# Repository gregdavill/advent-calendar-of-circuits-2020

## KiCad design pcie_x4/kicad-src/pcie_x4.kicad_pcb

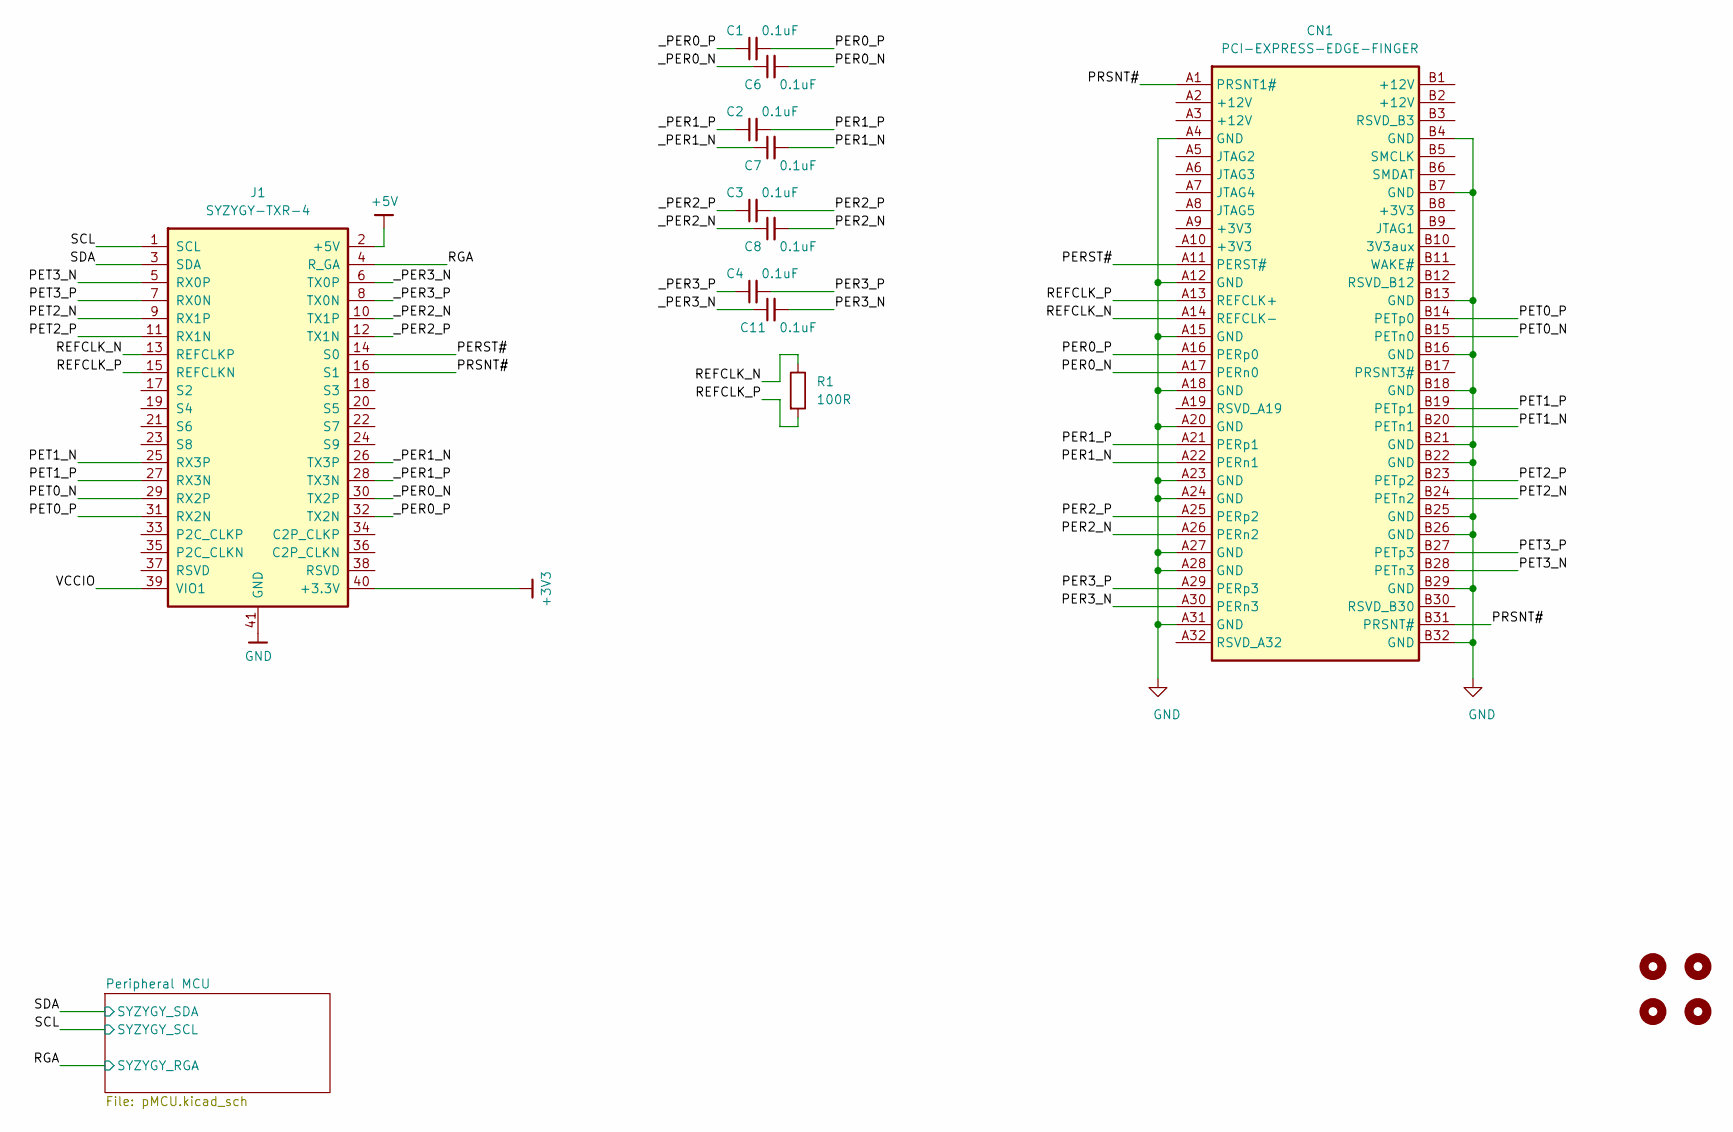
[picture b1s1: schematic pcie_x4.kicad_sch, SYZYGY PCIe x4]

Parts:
C1, C2, C3, C4, C6, C7, C8, C11: 0.1uF; C_0402_1005Metric
CN1: PCI-EXPRESS-EDGE-FINGER; BUS_PCIexpress_x4
H1, H2, H3, H4: MountingHole; MountingHole_3.2mm_M3
J1: SYZYGY-TXR-4; SYZYGY-TXR-POD
R1: 100R; R_0402_1005Metric

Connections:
+3V3: J1.40 (+3.3V); also elsewhere on the board
+5V: J1.2 (+5V)
/PER0_N: C6.2, CN1.A17 (PERn0)
/PER0_P: C1.2, CN1.A16 (PERp0)
/PER1_N: C7.2, CN1.A22 (PERn1)
/PER1_P: C2.2, CN1.A21 (PERp1)
/PER2_N: C8.2, CN1.A26 (PERn2)
/PER2_P: C3.2, CN1.A25 (PERp2)
/PER3_N: C11.2, CN1.A30 (PERn3)
/PER3_P: C4.2, CN1.A29 (PERp3)
/PERST#: CN1.A11 (PERST#), J1.14 (S0)
/PET0_N: CN1.B15 (PETn0), J1.29 (RX2P)
/PET0_P: CN1.B14 (PETp0), J1.31 (RX2N)
/PET1_N: CN1.B20 (PETn1), J1.25 (RX3P)
/PET1_P: CN1.B19 (PETp1), J1.27 (RX3N)
/PET2_N: CN1.B24 (PETn2), J1.9 (RX1P)
/PET2_P: CN1.B23 (PETp2), J1.11 (RX1N)
/PET3_N: CN1.B28 (PETn3), J1.5 (RX0P)
/PET3_P: CN1.B27 (PETp3), J1.7 (RX0N)
/PRSNT#: CN1.A1 (PRSNT1#), CN1.B31 (PRSNT#), J1.16 (S1)
/REFCLK_N: CN1.A14 (REFCLK-), J1.13 (REFCLKP), R1.1
/REFCLK_P: CN1.A13 (REFCLK+), J1.15 (REFCLKN), R1.2
/RGA: J1.4 (R_GA); also elsewhere on the board
/SCL: J1.1 (SCL); also elsewhere on the board
/SDA: J1.3 (SDA); also elsewhere on the board
/VCCIO: J1.39 (VIO1)
/_PER0_N: C6.1, J1.30 (TX2P)
/_PER0_P: C1.1, J1.32 (TX2N)
/_PER1_N: C7.1, J1.26 (TX3P)
/_PER1_P: C2.1, J1.28 (TX3N)
/_PER2_N: C8.1, J1.10 (TX1P)
/_PER2_P: C3.1, J1.12 (TX1N)
/_PER3_N: C11.1, J1.6 (TX0P)
/_PER3_P: C4.1, J1.8 (TX0N)
GND: CN1.A4 (GND), CN1.A12 (GND), CN1.A15 (GND), CN1.A18 (GND), CN1.A20 (GND), CN1.A23 (GND), CN1.A24 (GND), CN1.A27 (GND), CN1.A28 (GND), CN1.A31 (GND), CN1.B4 (GND), CN1.B7 (GND), CN1.B13 (GND), CN1.B16 (GND), CN1.B18 (GND), CN1.B21 (GND), CN1.B22 (GND), CN1.B25 (GND), CN1.B26 (GND), CN1.B29 (GND), CN1.B32 (GND), J1.41 (GND); also elsewhere on the board

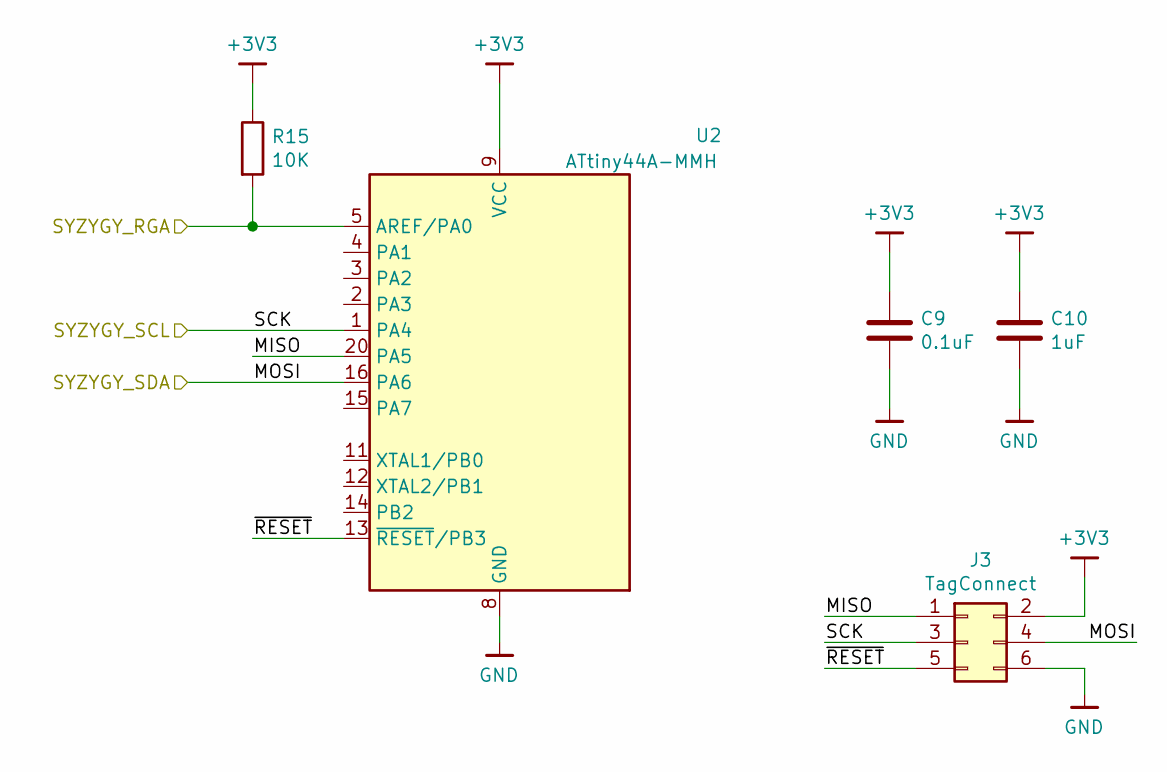
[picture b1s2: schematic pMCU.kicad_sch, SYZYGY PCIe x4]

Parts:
C9: 0.1uF; C_0402_1005Metric
C10: 1uF; C_0402_1005Metric
J3: TagConnect; TC2030-NL_SMALL
R15: 10K; R_0402_1005Metric
U2: ATtiny44A-MMH; QFN-20-1EP_3x3mm_P0.45mm_EP1.6x1.6mm

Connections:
+3V3: C9.1, C10.1, J3.2, R15.1, U2.9 (VCC); also elsewhere on the board
/Peripheral MCU/MISO: J3.1, U2.20 (PA5)
/Peripheral MCU/~RESET: J3.5, U2.13 (~RESET~/PB3)
/RGA: R15.2, U2.5 (AREF/PA0); also elsewhere on the board
/SCL: J3.3, U2.1 (PA4); also elsewhere on the board
/SDA: J3.4, U2.16 (PA6); also elsewhere on the board
GND: C9.2, C10.2, J3.6, U2.8 (GND), U2.21 (GND); also elsewhere on the board

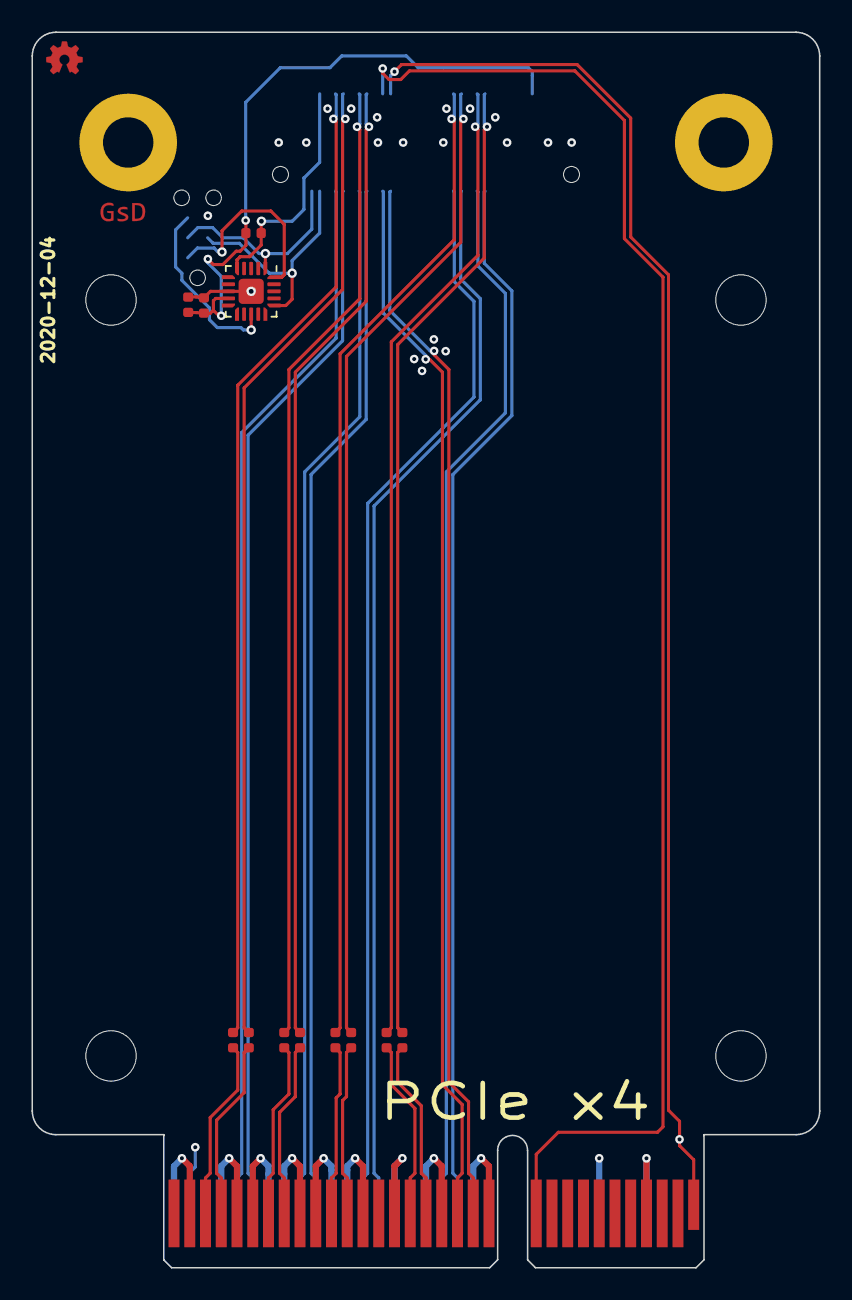
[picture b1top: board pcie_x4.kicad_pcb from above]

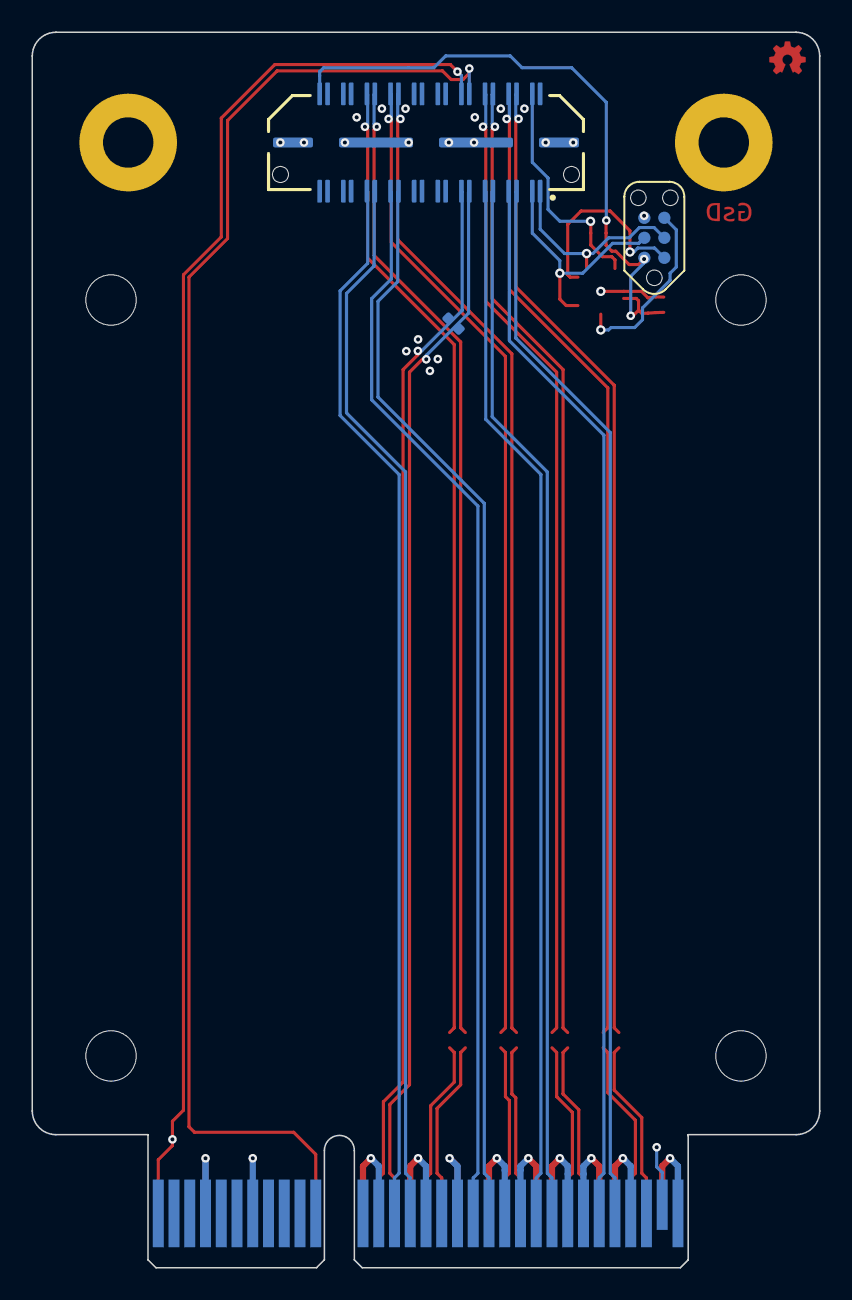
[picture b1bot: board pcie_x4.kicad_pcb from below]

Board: 4 copper layers, 50.0 x 78.5 mm, 20 parts (4 on the bottom side), 35 nets.

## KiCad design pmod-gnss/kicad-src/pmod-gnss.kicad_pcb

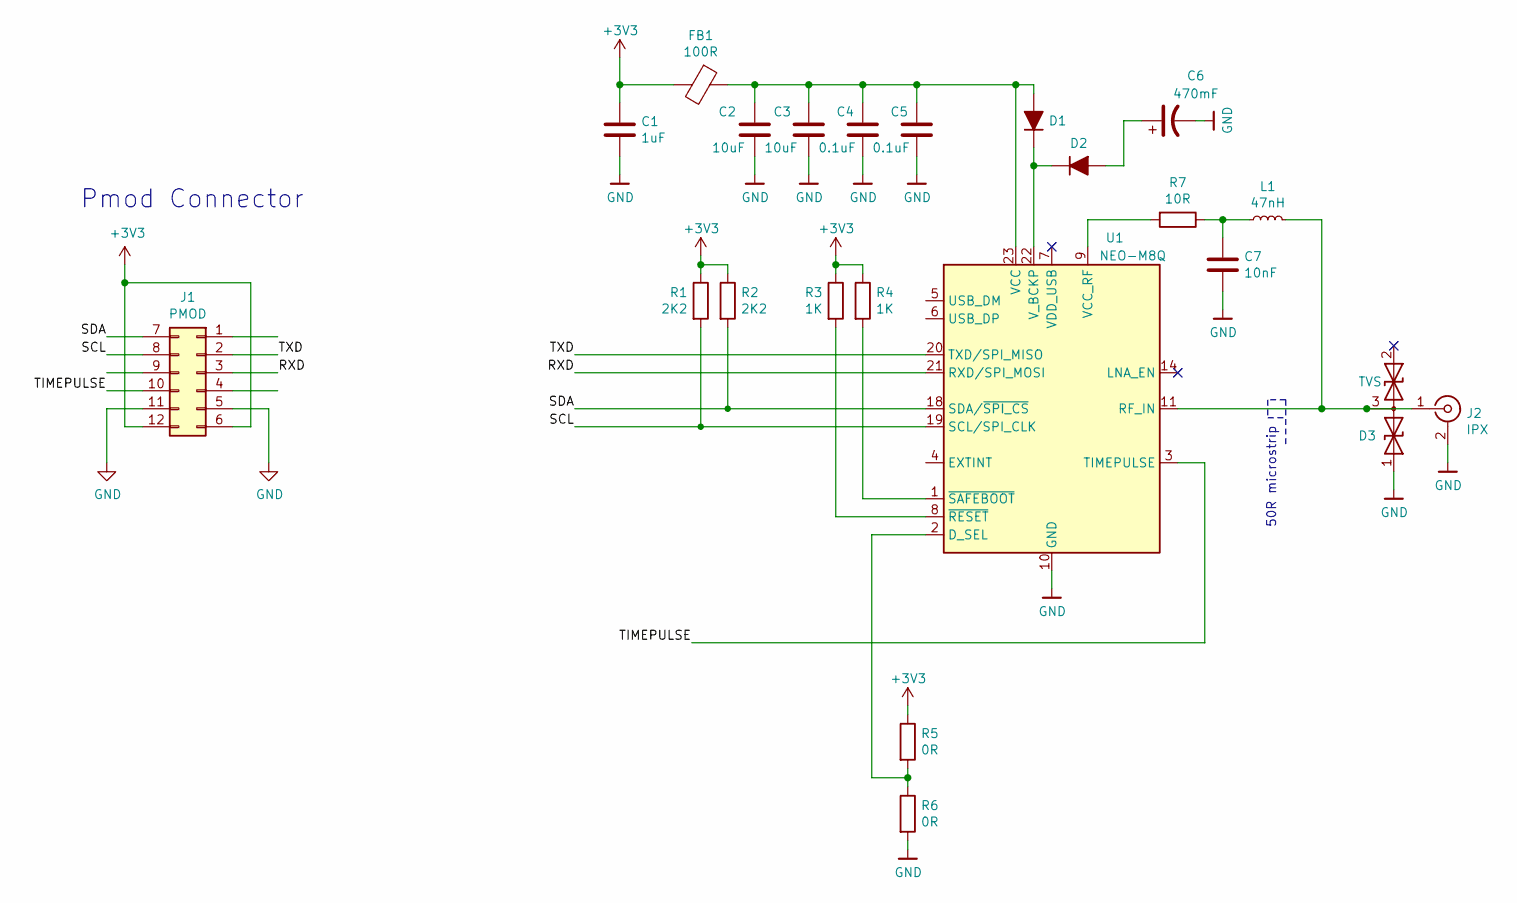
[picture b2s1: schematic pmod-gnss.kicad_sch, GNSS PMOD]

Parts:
C1: 1uF; C_0402_1005Metric
C2, C3: 10uF; C_0603_1608Metric
C4, C5: 0.1uF; C_0402_1005Metric
C6: 470mF; BatteryHolder_Keystone_2998_1x6.8mm
C7: 10nF; C_0402_1005Metric
D1, D2: D_ALT; D_SOD-123F
D3: TVS; SOT-323_SC-70
FB1: 100R; L_0603_1608Metric
J1: PMOD; PinHeader_2x06_P2.54mm_Horizontal
J2: IPX; SMA_Amphenol_132289_EdgeMount
L1: 47nH; L_0402_1005Metric
R1, R2: 2K2; R_0402_1005Metric
R3, R4: 1K; R_0402_1005Metric
R5, R6: 0R; R_0402_1005Metric
R7: 10R; R_0402_1005Metric
U1: NEO-M8Q; ublox_NEO

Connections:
+3V3: C1.1, FB1.2, J1.6, J1.12, R1.1, R2.1, R3.1, R4.1, R5.1
/RXD: J1.3, U1.21 (RXD/SPI_MOSI)
/SCL: J1.8, R1.2, U1.19 (SCL/SPI_CLK)
/SDA: J1.7, R2.2, U1.18 (SDA/~SPI_CS)
/TIMEPULSE: J1.10, U1.3 (TIMEPULSE)
/TXD: J1.2, U1.20 (TXD/SPI_MISO)
GND: C1.2, C2.2, C3.2, C4.2, C5.2, C6.2, C7.2, D3.1 (A1), J1.5, J1.11, J2.2 (Ext), R6.2, U1.10 (GND), U1.12 (GND), U1.13 (GND), U1.24 (GND)
unnamed: C2.1, C3.1, C4.1, C5.1, D1.2 (A), FB1.1, U1.23 (VCC)
unnamed: C6.1, D2.2 (A)
unnamed: C7.1, L1.1, R7.1
unnamed: D1.1 (K), D2.1 (K), U1.22 (V_BCKP)
unnamed: D3.3 (common), J2.1 (In), L1.2, U1.11 (RF_IN)
unnamed: R3.2, U1.8 (~RESET)
unnamed: R4.2, U1.1 (~SAFEBOOT)
unnamed: R5.2, R6.1, U1.2 (D_SEL)
unnamed: R7.2, U1.9 (VCC_RF)
no_connect_23: D3.2 (A2)
no_connect_24: U1.14 (LNA_EN)
no_connect_25: U1.15 (RESERVED)
no_connect_26: U1.16 (RESERVED)
no_connect_27: U1.17 (RESERVED)
no_connect_28: U1.7 (VDD_USB)

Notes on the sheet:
Pmod Connector
50R microstrip

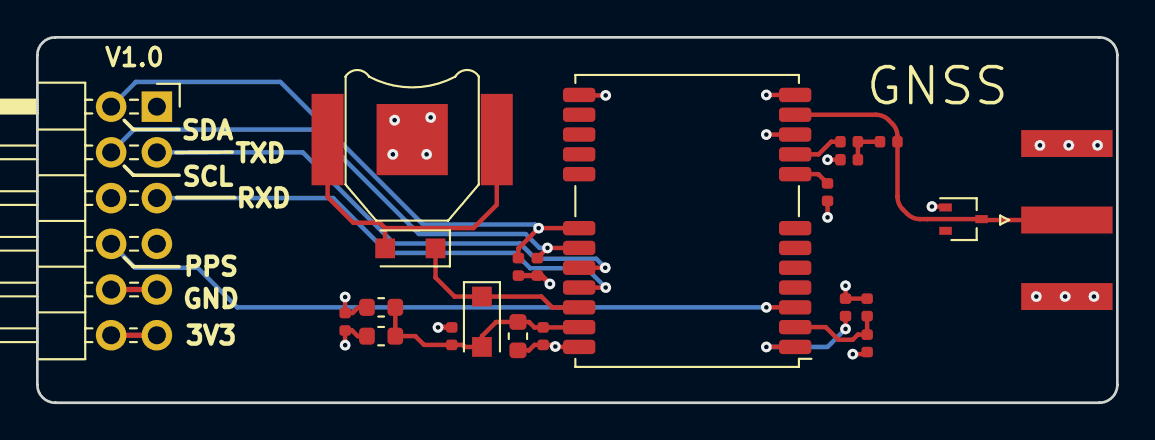
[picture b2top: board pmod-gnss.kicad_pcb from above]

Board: 4 copper layers, 60.0 x 20.3 mm, 22 parts (0 on the bottom side), 16 nets.

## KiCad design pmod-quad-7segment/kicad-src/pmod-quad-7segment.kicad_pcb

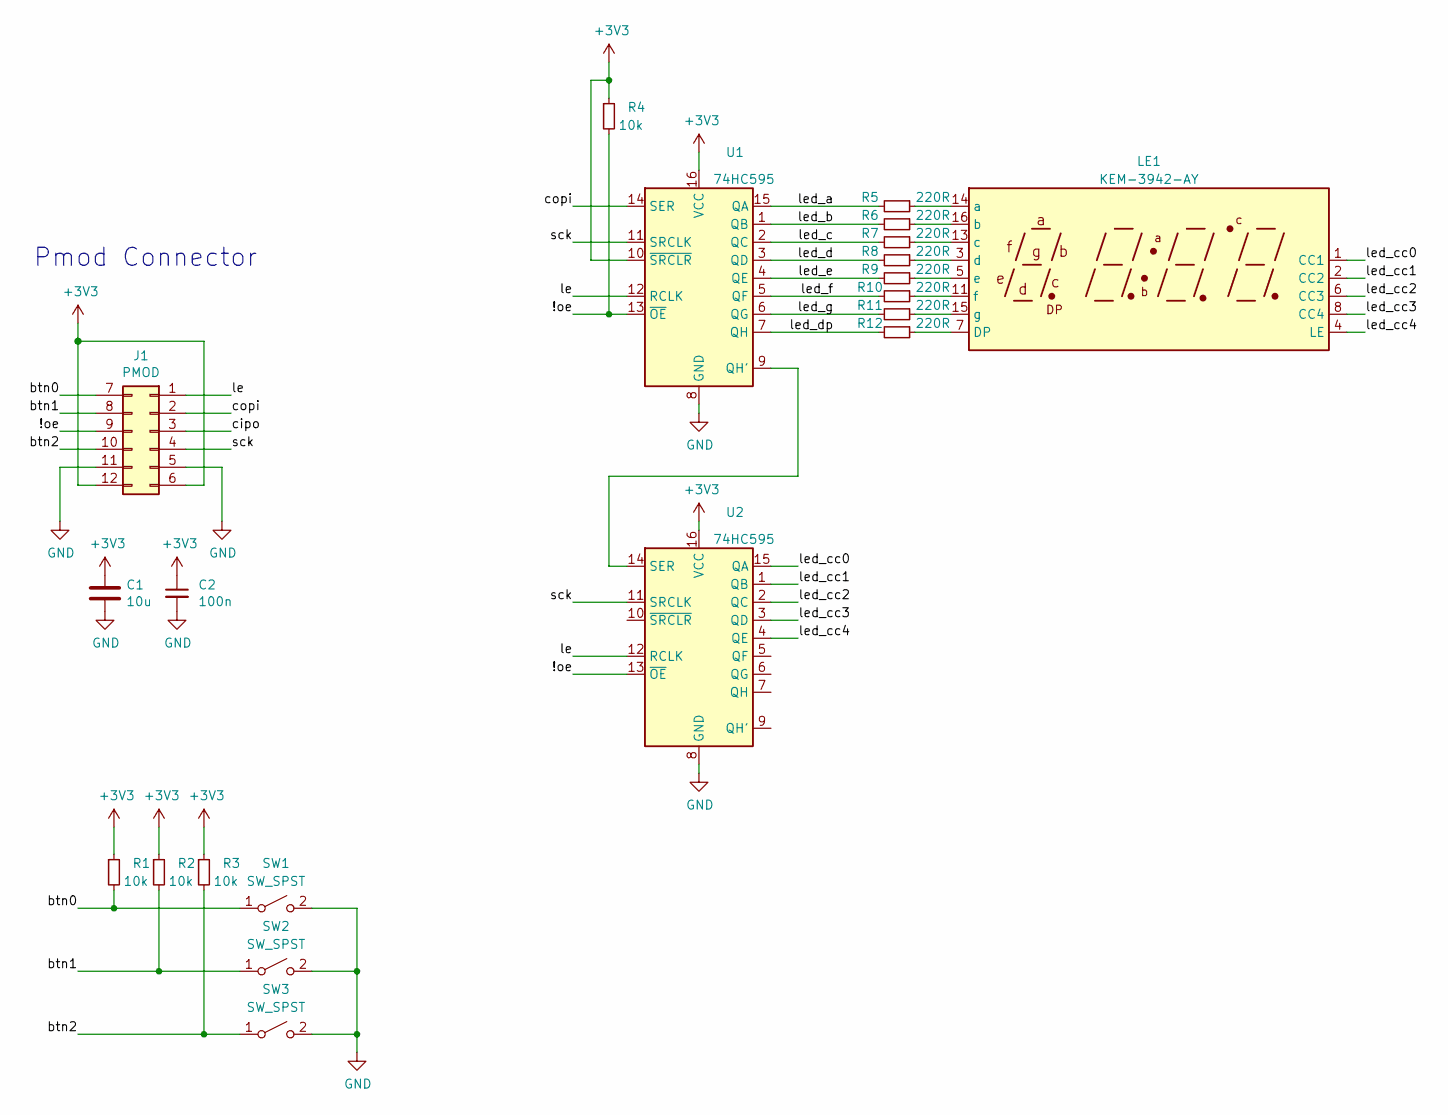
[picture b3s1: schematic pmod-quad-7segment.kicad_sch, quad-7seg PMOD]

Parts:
C1: 10u; C_0603_1608Metric
C2: 100n; C_0402_1005Metric
J1: PMOD; PinHeader_2x06_P2.54mm_Horizontal
LE1: KEM-3942-AY; kem-3942-ay
R1, R2, R3, R4: 10k; R_0402_1005Metric
R5, R6, R7, R8, R9, R10, R11, R12: 220R; R_0402_1005Metric
SW1, SW2, SW3: SW_SPST; SW_SPST_PTS810
U1, U2: 74HC595; TSSOP-16_4.4x5mm_P0.65mm

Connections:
+3V3: C1.1, C2.1, J1.6, J1.12, R1.1, R2.1, R3.1, R4.1, U1.10 (~SRCLR), U1.16 (VCC), U2.16 (VCC)
/!oe: J1.9, R4.2, U1.13 (~OE), U2.13 (~OE)
/btn0: J1.7, R1.2, SW1.1 (A)
/btn1: J1.8, R2.2, SW2.1 (A)
/btn2: J1.10, R3.2, SW3.1 (A)
/cipo: J1.3
/copi: J1.2, U1.14 (SER)
/le: J1.1, U1.12 (RCLK), U2.12 (RCLK)
/led_a: R5.2, U1.15 (QA)
/led_b: R6.2, U1.1 (QB)
/led_c: R7.2, U1.2 (QC)
/led_cc0: LE1.1 (CC1), U2.15 (QA)
/led_cc1: LE1.2 (CC2), U2.1 (QB)
/led_cc2: LE1.6 (CC3), U2.2 (QC)
/led_cc3: LE1.8 (CC4), U2.3 (QD)
/led_cc4: LE1.4 (LE), U2.4 (QE)
/led_d: R8.2, U1.3 (QD)
/led_dp: R12.2, U1.7 (QH)
/led_e: R9.2, U1.4 (QE)
/led_f: R10.2, U1.5 (QF)
/led_g: R11.2, U1.6 (QG)
/sck: J1.4, U1.11 (SRCLK), U2.11 (SRCLK)
GND: C1.2, C2.2, J1.5, J1.11, SW1.2 (B), SW2.2 (B), SW3.2 (B), U1.8 (GND), U2.8 (GND)
unnamed: LE1.3 (d), R8.1
unnamed: LE1.5 (e), R9.1
unnamed: LE1.7 (DP), R12.1
unnamed: LE1.11 (f), R10.1
unnamed: LE1.13 (c), R7.1
unnamed: LE1.14 (a), R5.1
unnamed: LE1.15 (g), R11.1
unnamed: LE1.16 (b), R6.1
unnamed: U1.9 (QH'), U2.14 (SER)

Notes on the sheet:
Pmod Connector

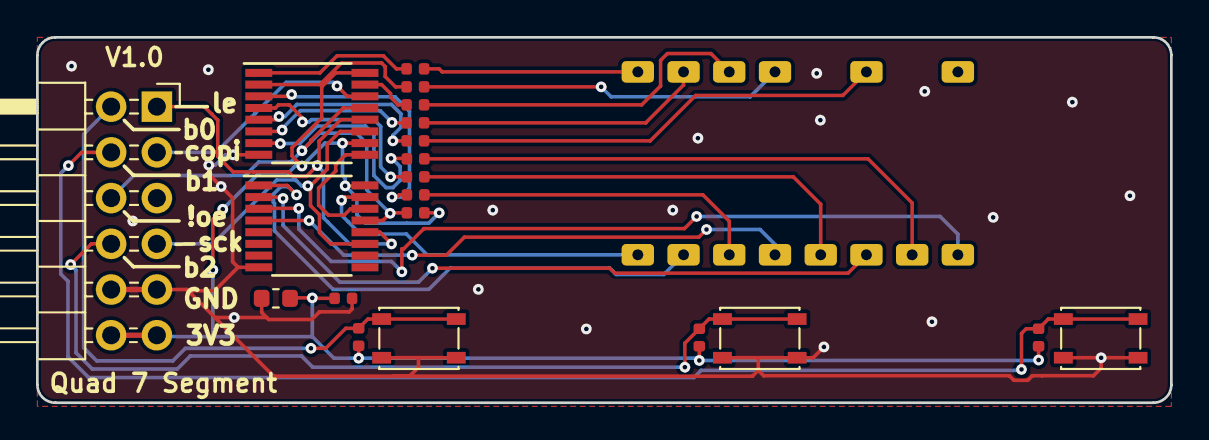
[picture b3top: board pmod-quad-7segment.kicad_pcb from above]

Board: 2 copper layers, 63.0 x 20.3 mm, 21 parts (0 on the bottom side), 31 nets.

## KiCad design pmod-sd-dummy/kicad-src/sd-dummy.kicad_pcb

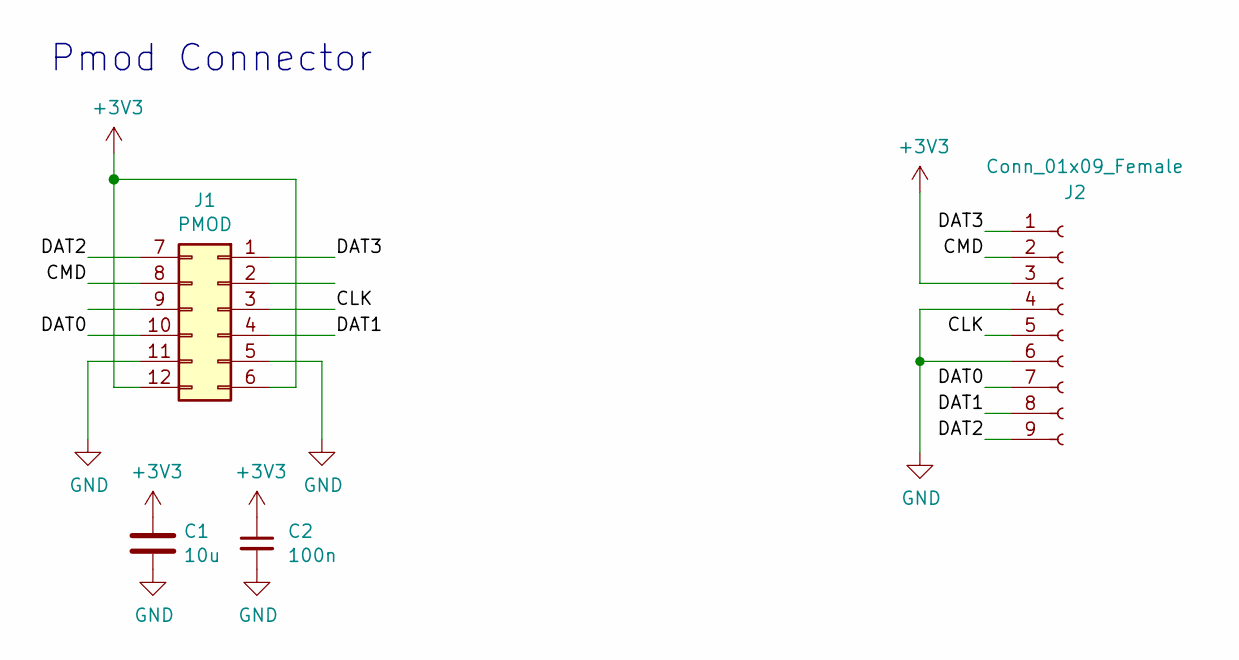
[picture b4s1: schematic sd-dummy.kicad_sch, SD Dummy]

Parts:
C1: 10u; C_0603_1608Metric
C2: 100n; C_0402_1005Metric
J1: PMOD; PinHeader_2x06_P2.54mm_Horizontal
J2: Conn_01x09_Female; SD_PCB

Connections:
+3V3: C1.1, C2.1, J1.6, J1.12, J2.3
/CLK: J1.3, J2.5
/CMD: J1.8, J2.2
/DAT0: J1.10, J2.7
/DAT1: J1.4, J2.8
/DAT2: J1.7, J2.9
/DAT3: J1.1, J2.1
GND: C1.2, C2.2, J1.5, J1.11, J2.4, J2.6

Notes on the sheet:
Pmod Connector

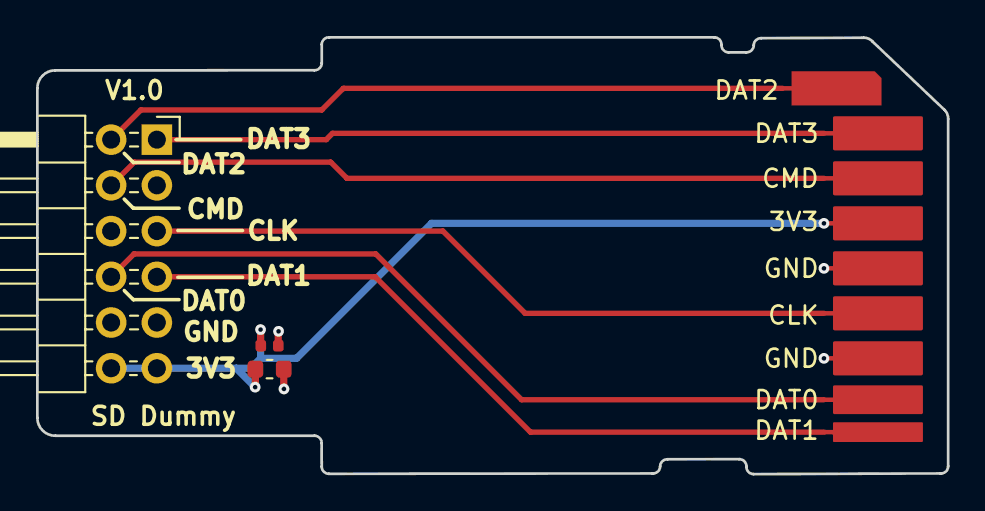
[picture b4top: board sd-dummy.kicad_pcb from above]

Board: 4 copper layers, 50.6 x 24.3 mm, 4 parts (0 on the bottom side), 8 nets.

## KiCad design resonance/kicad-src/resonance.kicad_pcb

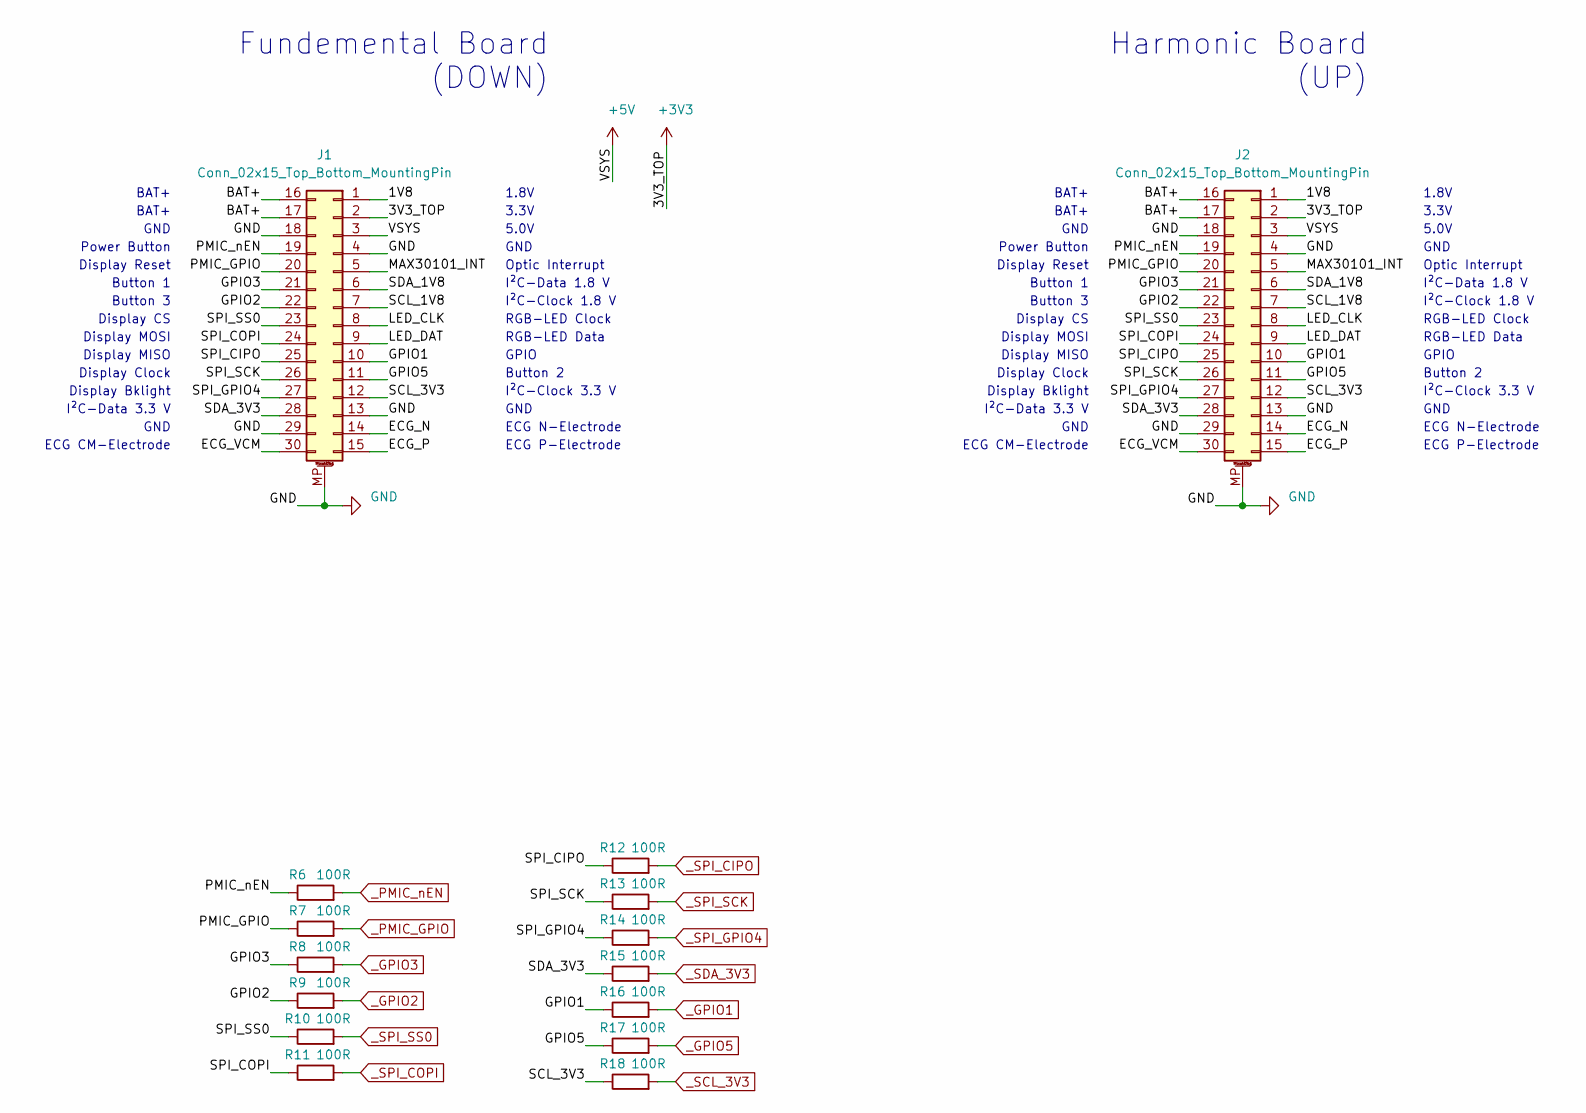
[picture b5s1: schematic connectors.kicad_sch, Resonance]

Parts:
J1: Conn_02x15_Top_Bottom_MountingPin; 10132797-035100LF
J2: Conn_02x15_Top_Bottom_MountingPin; 10132798-30
R6, R7, R8, R9, R10, R11, R12, R13, R14, R15, R16, R17, R18: 100R; R_0402_1005Metric

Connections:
+3V3: J1.2, J2.2; also elsewhere on the board
+5V: J1.3, J2.3; also elsewhere on the board
/Connectors/1V8: J1.1, J2.1
/Connectors/BAT+: J1.16, J1.17, J2.16, J2.17
/Connectors/ECG_N: J1.14, J2.14
/Connectors/ECG_P: J1.15, J2.15
/Connectors/ECG_VCM: J1.30, J2.30
/Connectors/GPIO1: J1.10, J2.10, R16.1
/Connectors/GPIO2: J1.22, J2.22, R9.1
/Connectors/GPIO3: J1.21, J2.21, R8.1
/Connectors/GPIO5: J1.11, J2.11, R17.1
/Connectors/LED_CLK: J1.8, J2.8
/Connectors/LED_DAT: J1.9, J2.9
/Connectors/MAX30101_INT: J1.5, J2.5
/Connectors/PMIC_GPIO: J1.20, J2.20, R7.1
/Connectors/PMIC_nEN: J1.19, J2.19, R6.1
/Connectors/SCL_1V8: J1.7, J2.7
/Connectors/SCL_3V3: J1.12, J2.12, R18.1
/Connectors/SDA_1V8: J1.6, J2.6
/Connectors/SDA_3V3: J1.28, J2.28, R15.1
/Connectors/SPI_CIPO: J1.25, J2.25, R12.1
/Connectors/SPI_COPI: J1.24, J2.24, R11.1
/Connectors/SPI_GPIO4: J1.27, J2.27, R14.1
/Connectors/SPI_SCK: J1.26, J2.26, R13.1
/Connectors/SPI_SS0: J1.23, J2.23, R10.1
GND: J1.4, J1.13, J1.18, J1.29, J1.MP (MountPin), J2.4, J2.13, J2.18, J2.29, J2.MP (MountPin); also elsewhere on the board
_GPIO1: R16.2; also elsewhere on the board
_GPIO2: R9.2; also elsewhere on the board
_GPIO3: R8.2; also elsewhere on the board
_GPIO5: R17.2; also elsewhere on the board
_PMIC_GPIO: R7.2; also elsewhere on the board
_PMIC_nEN: R6.2; also elsewhere on the board
_SCL_3V3: R18.2; also elsewhere on the board
_SDA_3V3: R15.2; also elsewhere on the board
_SPI_CIPO: R12.2; also elsewhere on the board
_SPI_COPI: R11.2; also elsewhere on the board
_SPI_GPIO4: R14.2; also elsewhere on the board
_SPI_SCK: R13.2; also elsewhere on the board
_SPI_SS0: R10.2; also elsewhere on the board

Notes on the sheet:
BAT+
GND
Power Button
Display Reset
Button 1
Button 3
Display CS
Display MOSI
Display MISO
Display Clock
Display Bklight
I²C-Data 3.3 V
ECG CM-Electrode
1.8V
3.3V
5.0V
Optic Interrupt
I²C-Data 1.8 V
I²C-Clock 1.8 V
RGB-LED Clock
RGB-LED Data
GPIO
Button 2
I²C-Clock 3.3 V
ECG N-Electrode
ECG P-Electrode
Fundemental Board (DOWN)
Harmonic Board (UP)

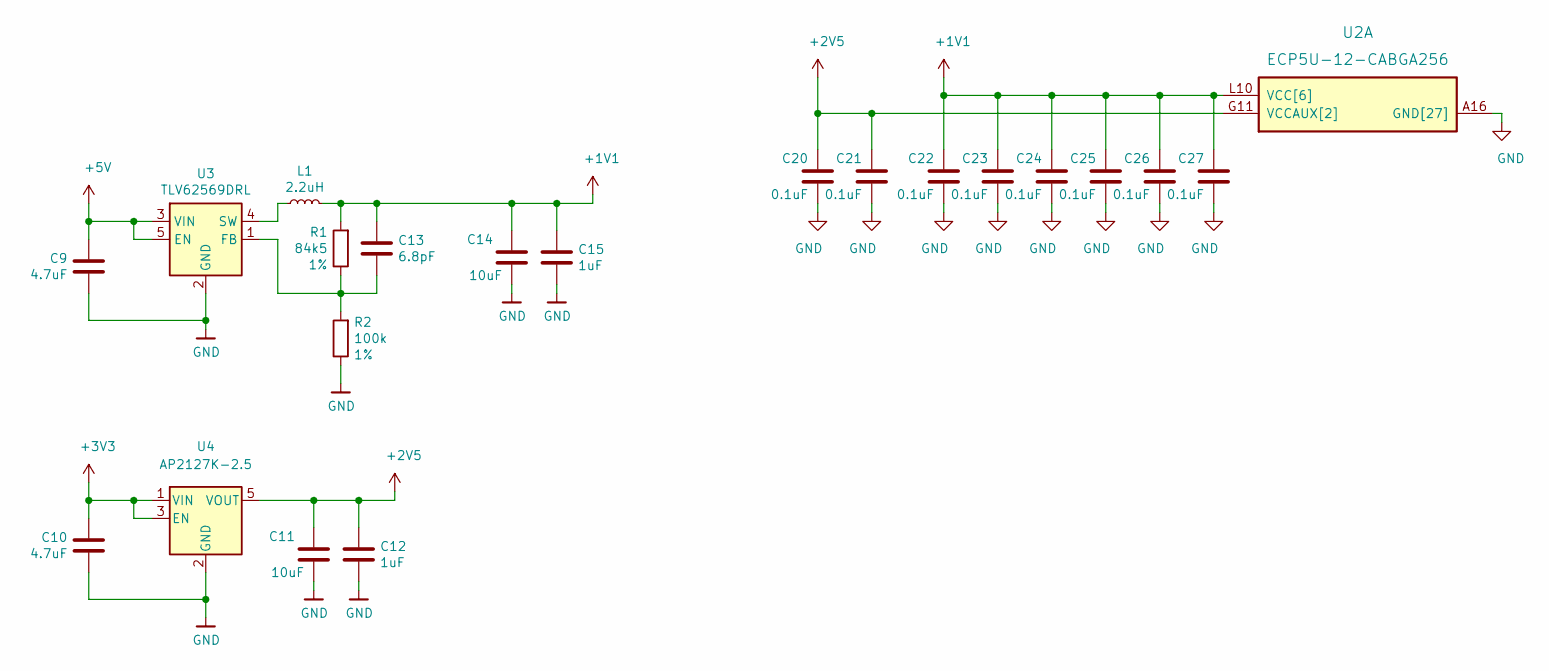
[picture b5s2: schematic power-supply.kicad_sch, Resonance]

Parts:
C9, C10: 4.7uF; C_0402_1005Metric
C11, C14: 10uF; C_0603_1608Metric
C12, C15: 1uF; C_0402_1005Metric
C13: 6.8pF; C_0402_1005Metric
C20, C21, C22, C23, C24, C25, C26, C27: 0.1uF; C_0402_1005Metric
L1: 2.2uH; L_0805_2012Metric
R1: 84k5; R_0402_1005Metric
R2: 100k; R_0402_1005Metric
U2: ECP5U-12-CABGA256; BGA-256_14.0x14.0mm_Layout16x16_P0.8mm_Ball0.45mm_Pad0.32mm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
U3: TLV62569DRL; SOT-666
U4: AP2127K-2.5; SOT-23-5

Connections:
+1V1: C13.1, C14.1, C15.1, C22.1, C23.1, C24.1, C25.1, C26.1, C27.1, L1.2, R1.2, U2.G6 (VCC[6]), U2.G7 (VCC[6]), U2.G9 (VCC[6]), U2.L8 (VCC[6]), U2.L9 (VCC[6]), U2.L10 (VCC[6])
+2V5: C11.1, C12.1, C20.1, C21.1, U2.G11 (VCCAUX[2]), U2.L7 (VCCAUX[2]), U4.5 (VOUT)
+3V3: C10.1, U4.1 (VIN), U4.3 (EN); also elsewhere on the board
+5V: C9.1, U3.3 (VIN), U3.5 (EN); also elsewhere on the board
GND: C9.2, C10.2, C11.2, C12.2, C14.2, C15.2, C20.2, C21.2, C22.2, C23.2, C24.2, C25.2, C26.2, C27.2, R2.1, U2.A1 (GND[27]), U2.A16 (GND[27]), U2.D2 (GND[27]), U2.D15 (GND[27]), U2.F8 (GND[27]), U2.F9 (GND[27]), U2.G8 (GND[27]), U2.G10 (GND[27]), U2.H1 (GND[27]), U2.H8 (GND[27]), U2.H9 (GND[27]), U2.H10 (GND[27]), U2.H16 (GND[27]), U2.J8 (GND[27]), U2.J9 (GND[27]), U2.J10 (GND[27]), U2.K6 (GND[27]), U2.K7 (GND[27]), U2.K8 (GND[27]), U2.K9 (GND[27]), U2.K10 (GND[27]), U2.N2 (GND[27]), U2.N15 (GND[27]), U2.T1 (GND[27]), U2.T5 (GND[27]), U2.T12 (GND[27]), U2.T16 (GND[27]), U3.2 (GND), U4.2 (GND); also elsewhere on the board
unnamed: C13.2, R1.1, R2.2, U3.1 (FB)
unnamed: L1.1, U3.4 (SW)
